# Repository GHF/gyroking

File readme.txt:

gyroking - firmware for the Gyro King 3lb battle bot
========
Xo Wang (http://www.geekshavefeelings.com)
Aaron Fan (http://aaronbot3000.blogspot.com)

About
-----
:D

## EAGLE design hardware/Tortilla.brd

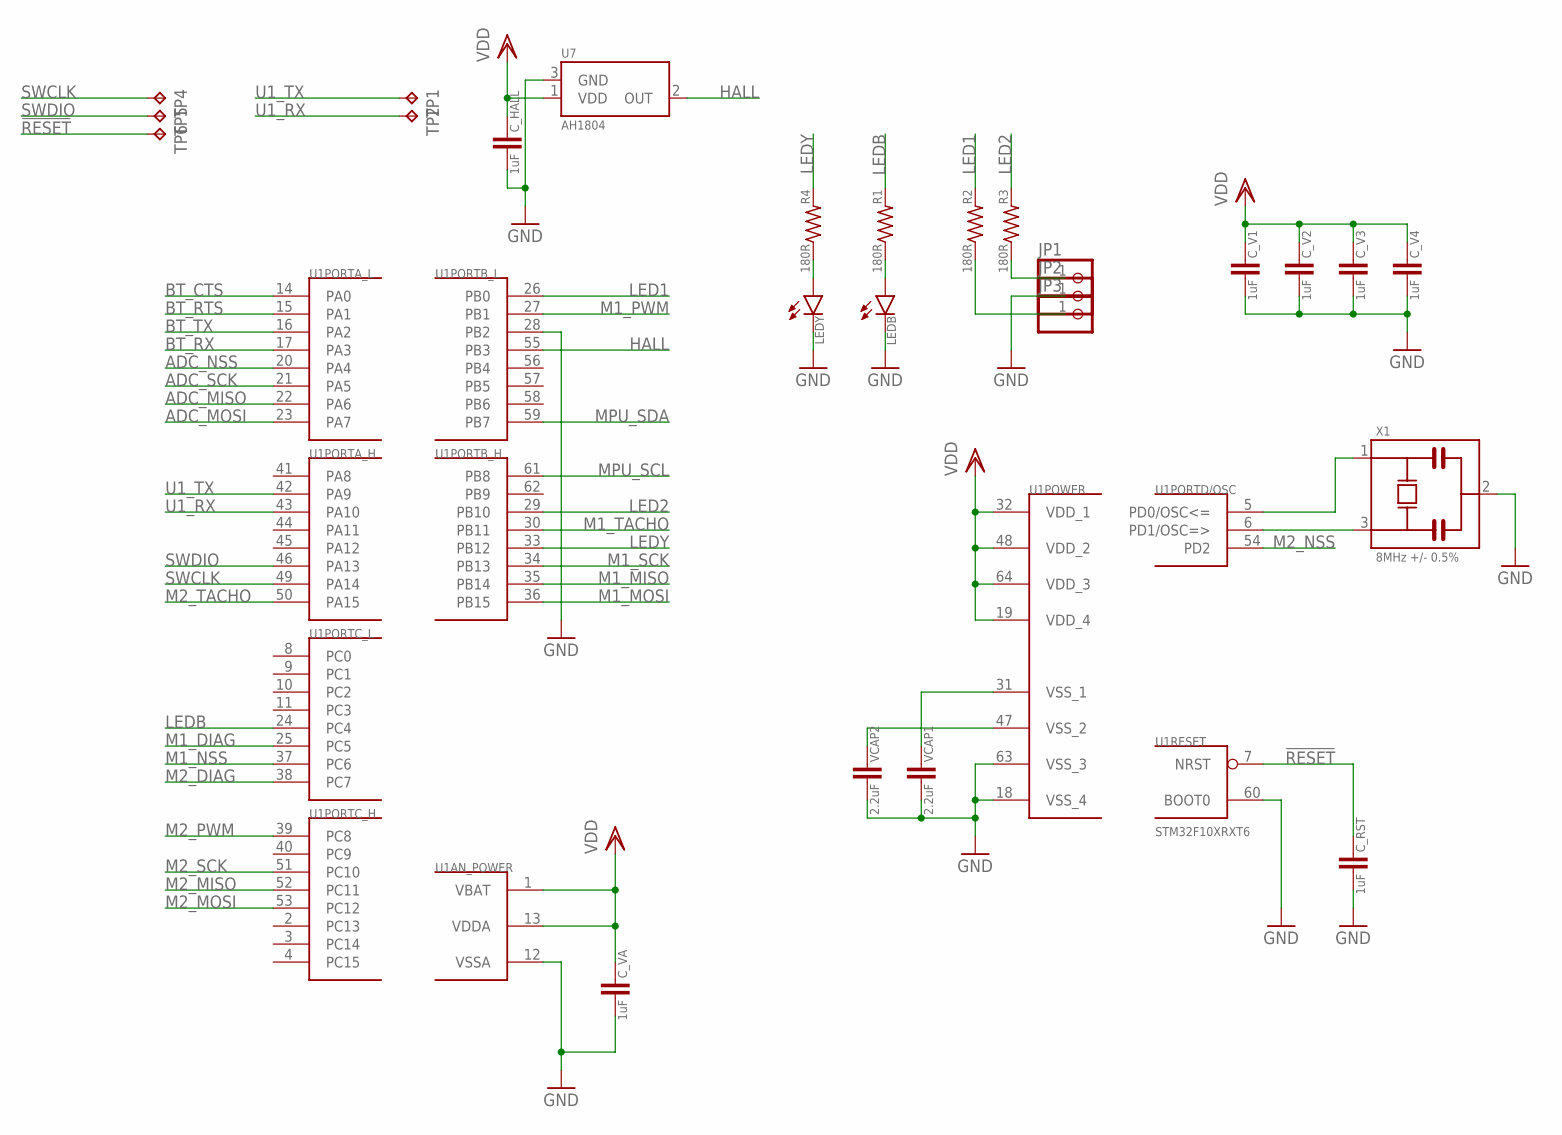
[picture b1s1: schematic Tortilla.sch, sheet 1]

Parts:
C_HALL: 1uF; 0603
C_RST: 1uF; 0603
C_V1, C_V2, C_V3, C_V4: 1uF; 0603
C_VA: 1uF; 0603
JP1, JP2, JP3: PINHD-1X1; 1X01
LEDB: LED0805; 0805_POL
LEDY: LED0805; 0805_POL
R1, R2, R3, R4: 180R; 0603
TP1, TP2, TP4, TP5, TP6: TPB1,27; B1,27
U1: STM32F10XRXT6; TQFP64
U7: AH1804; SOT23-3
VCAP1, VCAP2: 2.2uF; 0603
X1: 8MHz +/- 0.5%; MURATA_CSTCE

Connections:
!RESET: C_RST.1, TP6.TP, U1.7 (NRST)
ADC_MISO: U1.22 (PA6); also elsewhere on the board
ADC_MOSI: U1.23 (PA7); also elsewhere on the board
ADC_NSS: U1.20 (PA4); also elsewhere on the board
ADC_SCK: U1.21 (PA5); also elsewhere on the board
BT_CTS: U1.14 (PA0); also elsewhere on the board
BT_RTS: U1.15 (PA1); also elsewhere on the board
BT_RX: U1.17 (PA3); also elsewhere on the board
BT_TX: U1.16 (PA2); also elsewhere on the board
GND: C_HALL.2, C_RST.2, C_V1.2, C_V2.2, C_V3.2, C_V4.2, C_VA.2, JP2.1, LEDB.- (C), LEDY.- (C), U1.12 (VSSA), U1.18 (VSS_4), U1.28 (PB2), U1.60 (BOOT0), U1.63 (VSS_3), U7.3 (GND), VCAP1.2, VCAP2.2, X1.2; also elsewhere on the board
HALL: U1.55 (PB3), U7.2 (OUT)
LED1: R2.2, U1.26 (PB0)
LED2: R3.2, U1.29 (PB10)
LEDB: R1.2, U1.24 (PC4)
LEDY: R4.2, U1.33 (PB12)
M1_DIAG: U1.25 (PC5); also elsewhere on the board
M1_MISO: U1.35 (PB14); also elsewhere on the board
M1_MOSI: U1.36 (PB15); also elsewhere on the board
M1_NSS: U1.37 (PC6); also elsewhere on the board
M1_PWM: U1.27 (PB1); also elsewhere on the board
M1_SCK: U1.34 (PB13); also elsewhere on the board
M1_TACHO: U1.30 (PB11); also elsewhere on the board
M2_DIAG: U1.38 (PC7); also elsewhere on the board
M2_MISO: U1.52 (PC11); also elsewhere on the board
M2_MOSI: U1.53 (PC12); also elsewhere on the board
M2_NSS: U1.54 (PD2); also elsewhere on the board
M2_PWM: U1.39 (PC8); also elsewhere on the board
M2_SCK: U1.51 (PC10); also elsewhere on the board
M2_TACHO: U1.50 (PA15); also elsewhere on the board
MPU_SCL: U1.61 (PB8); also elsewhere on the board
MPU_SDA: U1.59 (PB7); also elsewhere on the board
unnamed: U1.6 (PD1/OSC=>), X1.3
unnamed: U1.5 (PD0/OSC<=), X1.1
unnamed: U1.47 (VSS_2), VCAP2.1
unnamed: U1.31 (VSS_1), VCAP1.1
unnamed: LEDB.+ (A), R1.1
unnamed: JP1.1, R3.1
unnamed: JP3.1, R2.1
unnamed: LEDY.+ (A), R4.1
SWCLK: TP4.TP, U1.49 (PA14)
SWDIO: TP5.TP, U1.46 (PA13)
U1_RX: TP2.TP, U1.43 (PA10)
U1_TX: TP1.TP, U1.42 (PA9)
VDD: C_HALL.1, C_V1.1, C_V2.1, C_V3.1, C_V4.1, C_VA.1, U1.1 (VBAT), U1.13 (VDDA), U1.19 (VDD_4), U1.32 (VDD_1), U1.48 (VDD_2), U1.64 (VDD_3), U7.1 (VDD); also elsewhere on the board

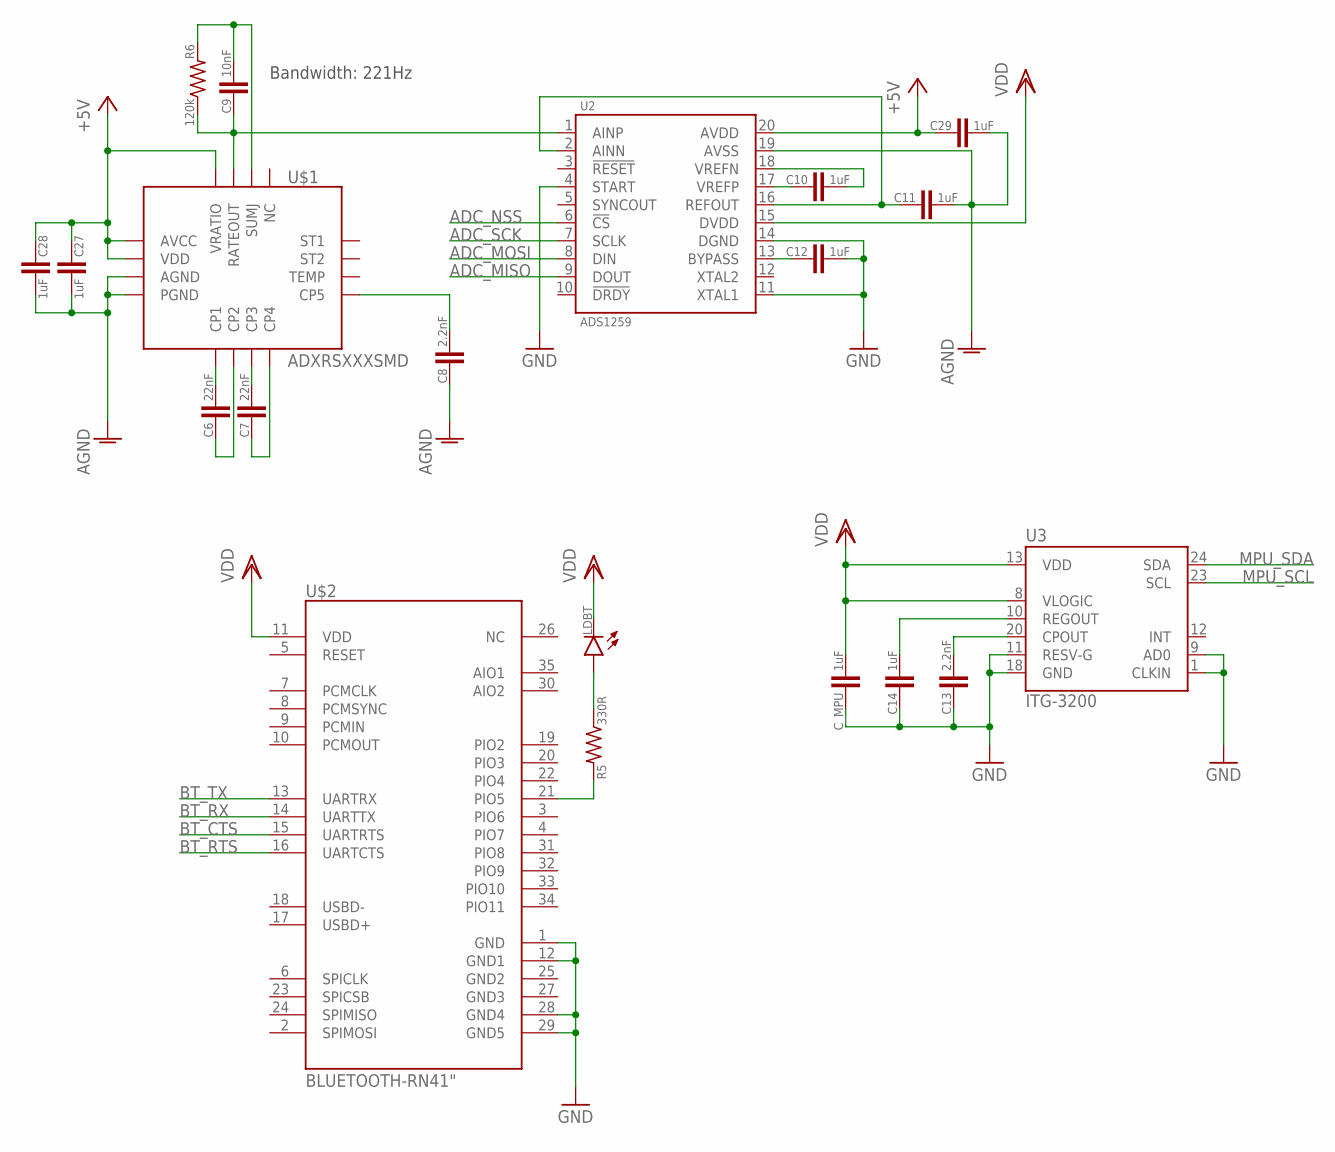
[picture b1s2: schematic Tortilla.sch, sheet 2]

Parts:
C6, C7: 22nF; 0603
C8, C13: 2.2nF; 0603
C9: 10nF; 0603
C10, C11, C12, C14, C27, C28, C29: 1uF; 0603
C_MPU: 1uF; 0603
LDBT: LED0805; 0805_POL
R5: 330R; 0603
R6: 120k; 0603
U2: ADS1259; TSSOP-20
U3: ITG-3200; QFN-24
U$1: ADXRSXXXSMD; BC-32
U$2: BLUETOOTH-RN41"; RN41

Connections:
+5V: C27.1, C28.1, C29.1, U2.20 (AVDD), U$1.AVCC, U$1.VDD, U$1.VRATIO; also elsewhere on the board
ADC_MISO: U2.9 (DOUT); also elsewhere on the board
ADC_MOSI: U2.8 (DIN); also elsewhere on the board
ADC_NSS: U2.6 (!CS); also elsewhere on the board
ADC_SCK: U2.7 (SCLK); also elsewhere on the board
AGND: C8.1, C11.2, C27.2, C28.2, C29.2, U2.19 (AVSS), U$1.AGND, U$1.PGND; also elsewhere on the board
BT_CTS: U$2.15 (UARTRTS); also elsewhere on the board
BT_RTS: U$2.16 (UARTCTS); also elsewhere on the board
BT_RX: U$2.14 (UARTTX); also elsewhere on the board
BT_TX: U$2.13 (UARTRX); also elsewhere on the board
GND: C12.2, C13.1, C14.1, C_MPU.1, U2.4 (START), U2.11 (XTAL1), U2.14 (DGND), U3.1 (CLKIN), U3.9 (AD0), U3.11 (RESV-G), U3.18 (GND), U$2.1 (GND), U$2.12 (GND1), U$2.28 (GND4), U$2.29 (GND5); also elsewhere on the board
MPU_SCL: U3.23 (SCL); also elsewhere on the board
MPU_SDA: U3.24 (SDA); also elsewhere on the board
unnamed: C6.2, U$1.CP1
unnamed: C6.1, U$1.CP2
unnamed: C7.2, U$1.CP3
unnamed: C7.1, U$1.CP4
unnamed: C8.2, U$1.CP5
unnamed: C9.1, R6.1, U2.1 (AINP), U$1.RATEOUT
unnamed: C9.2, R6.2, U$1.SUMJ
unnamed: C11.1, U2.2 (AINN), U2.16 (REFOUT)
unnamed: C10.2, U2.18 (VREFN)
unnamed: C10.1, U2.17 (VREFP)
unnamed: C12.1, U2.13 (BYPASS)
unnamed: C13.2, U3.20 (CPOUT)
unnamed: C14.2, U3.10 (REGOUT)
unnamed: R5.2, U$2.21 (PIO5)
unnamed: LDBT.+ (A), R5.1
VDD: C_MPU.2, LDBT.- (C), U2.15 (DVDD), U3.8 (VLOGIC), U3.13 (VDD), U$2.11 (VDD); also elsewhere on the board

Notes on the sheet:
Bandwidth: 221Hz

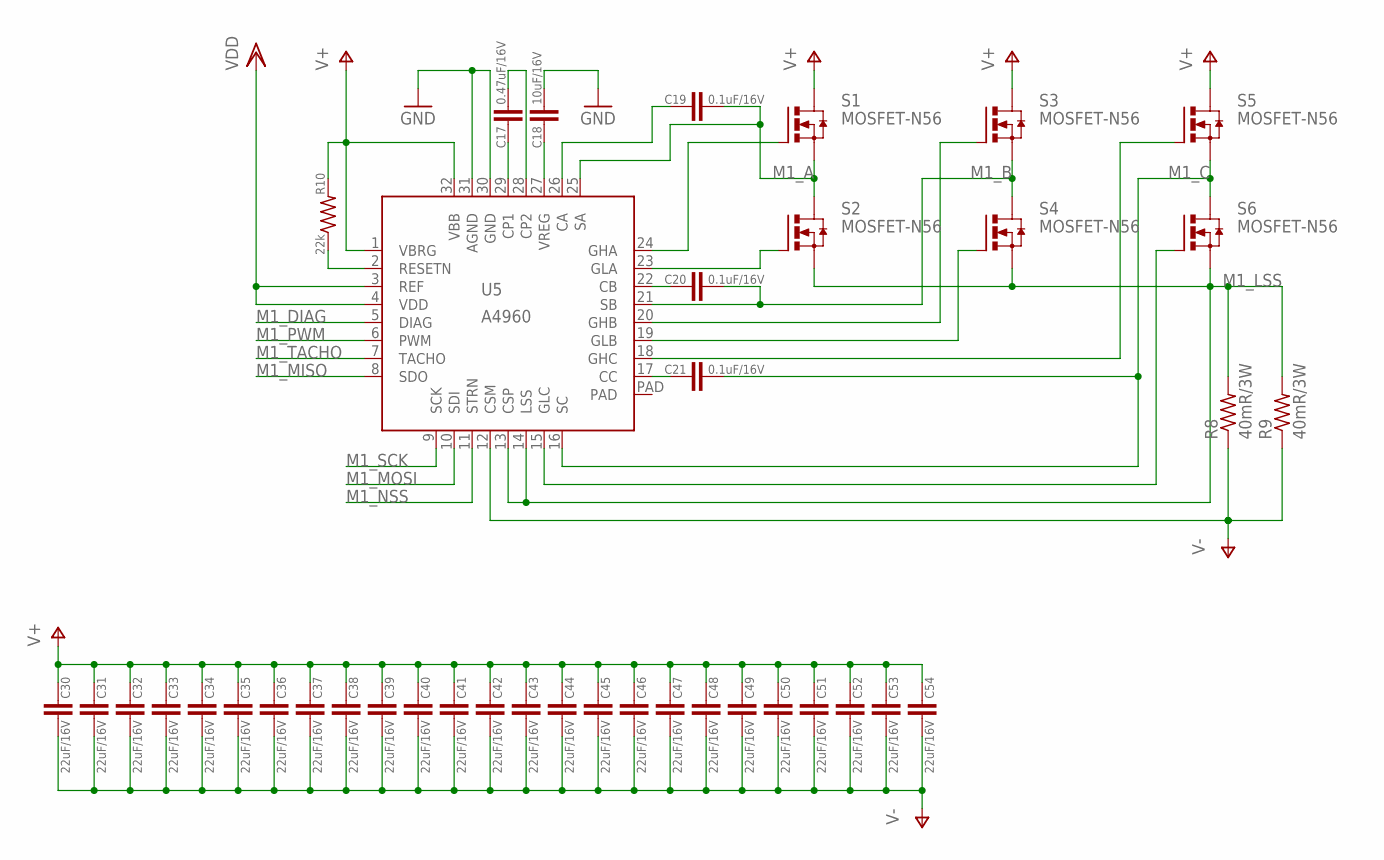
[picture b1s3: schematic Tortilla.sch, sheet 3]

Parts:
C17: 0.47uF/16V; 0603
C18: 10uF/16V; 0805
C19, C20, C21: 0.1uF/16V; 0603
C30, C31, C32, C33, C34, C35, C36, C37, C38, C39, C40, C41, C42, C43, C44, C45, C46, C47, C48, C49, C50, C51, C52, C53, C54: 22uF/16V; 1206
R8, R9: 40mR/3W; R2512
R10: 22k; 0603
S1, S2, S3, S4, S5, S6: MOSFET-N56; SON-5X6
U5: A4960; LQFP32-THERMPAD

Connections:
GND: C18.2, U5.30 (GND), U5.31 (AGND); also elsewhere on the board
M1_A: C19.2, S1.S1 (S), S1.S2 (S), S1.S3 (S), S2.D, U5.25 (SA)
M1_B: C20.2, S3.S1 (S), S3.S2 (S), S3.S3 (S), S4.D, U5.21 (SB)
M1_C: C21.2, S5.S1 (S), S5.S2 (S), S5.S3 (S), S6.D, U5.16 (SC)
M1_DIAG: U5.5 (DIAG); also elsewhere on the board
M1_LSS: R8.2, R9.2, S2.S1 (S), S2.S2 (S), S2.S3 (S), S4.S1 (S), S4.S2 (S), S4.S3 (S), S6.S1 (S), S6.S2 (S), S6.S3 (S), U5.13 (CSP), U5.14 (LSS)
M1_MISO: U5.8 (SDO); also elsewhere on the board
M1_MOSI: U5.10 (SDI); also elsewhere on the board
M1_NSS: U5.11 (STRN); also elsewhere on the board
M1_PWM: U5.6 (PWM); also elsewhere on the board
M1_SCK: U5.9 (SCK); also elsewhere on the board
M1_TACHO: U5.7 (TACHO); also elsewhere on the board
unnamed: C17.1, U5.29 (CP1)
unnamed: C17.2, U5.28 (CP2)
unnamed: C18.1, U5.27 (VREG)
unnamed: S1.G, U5.24 (GHA)
unnamed: S2.G, U5.23 (GLA)
unnamed: C19.1, U5.26 (CA)
unnamed: S3.G, U5.20 (GHB)
unnamed: S4.G, U5.19 (GLB)
unnamed: C20.1, U5.22 (CB)
unnamed: S5.G, U5.18 (GHC)
unnamed: S6.G, U5.15 (GLC)
unnamed: C21.1, U5.17 (CC)
unnamed: R10.1, U5.2 (RESETN)
V+: C30.1, C31.1, C32.1, C33.1, C34.1, C35.1, C36.1, C37.1, C38.1, C39.1, C40.1, C41.1, C42.1, C43.1, C44.1, C45.1, C46.1, C47.1, C48.1, C49.1, C50.1, C51.1, C52.1, C53.1, C54.1, R10.2, S1.D, S3.D, S5.D, U5.1 (VBRG), U5.32 (VBB); also elsewhere on the board
V-: C30.2, C31.2, C32.2, C33.2, C34.2, C35.2, C36.2, C37.2, C38.2, C39.2, C40.2, C41.2, C42.2, C43.2, C44.2, C45.2, C46.2, C47.2, C48.2, C49.2, C50.2, C51.2, C52.2, C53.2, C54.2, R8.1, R9.1, U5.12 (CSM); also elsewhere on the board
VDD: U5.3 (REF), U5.4 (VDD); also elsewhere on the board

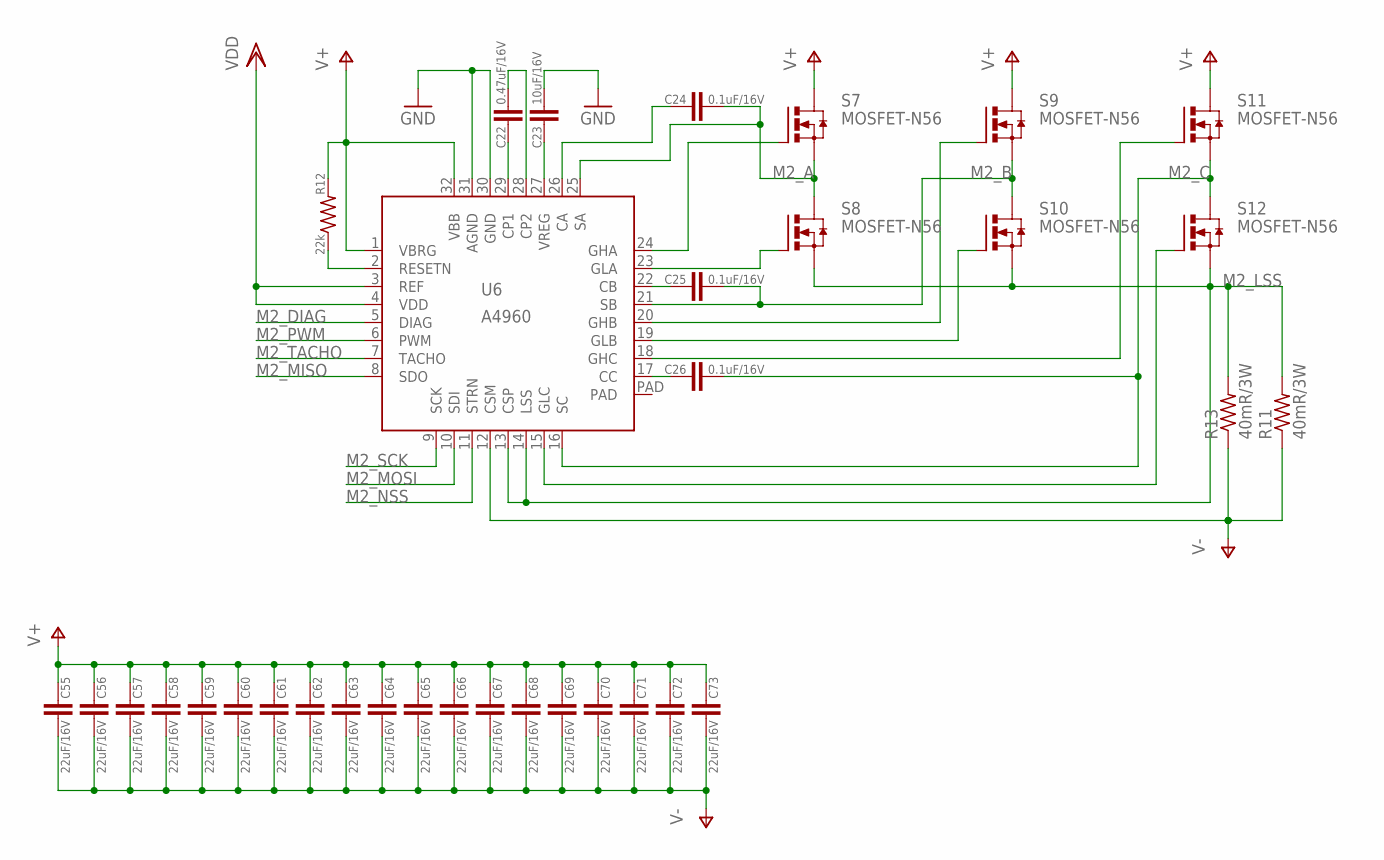
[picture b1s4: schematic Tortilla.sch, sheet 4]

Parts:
C22: 0.47uF/16V; 0603
C23: 10uF/16V; 0805
C24, C25, C26: 0.1uF/16V; 0603
C55, C56, C57, C58, C59, C60, C61, C62, C63, C64, C65, C66, C67, C68, C69, C70, C71, C72, C73: 22uF/16V; 1206
R11, R13: 40mR/3W; R2512
R12: 22k; 0603
S7, S8, S9, S10, S11, S12: MOSFET-N56; SON-5X6
U6: A4960; LQFP32-THERMPAD

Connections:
GND: C23.2, U6.30 (GND), U6.31 (AGND); also elsewhere on the board
M2_A: C24.2, S7.S1 (S), S7.S2 (S), S7.S3 (S), S8.D, U6.25 (SA)
M2_B: C25.2, S9.S1 (S), S9.S2 (S), S9.S3 (S), S10.D, U6.21 (SB)
M2_C: C26.2, S11.S1 (S), S11.S2 (S), S11.S3 (S), S12.D, U6.16 (SC)
M2_DIAG: U6.5 (DIAG); also elsewhere on the board
M2_LSS: R11.2, R13.2, S8.S1 (S), S8.S2 (S), S8.S3 (S), S10.S1 (S), S10.S2 (S), S10.S3 (S), S12.S1 (S), S12.S2 (S), S12.S3 (S), U6.13 (CSP), U6.14 (LSS)
M2_MISO: U6.8 (SDO); also elsewhere on the board
M2_MOSI: U6.10 (SDI); also elsewhere on the board
M2_NSS: U6.11 (STRN); also elsewhere on the board
M2_PWM: U6.6 (PWM); also elsewhere on the board
M2_SCK: U6.9 (SCK); also elsewhere on the board
M2_TACHO: U6.7 (TACHO); also elsewhere on the board
unnamed: C22.2, U6.28 (CP2)
unnamed: C22.1, U6.29 (CP1)
unnamed: C23.1, U6.27 (VREG)
unnamed: S7.G, U6.24 (GHA)
unnamed: S8.G, U6.23 (GLA)
unnamed: C24.1, U6.26 (CA)
unnamed: S9.G, U6.20 (GHB)
unnamed: S10.G, U6.19 (GLB)
unnamed: C25.1, U6.22 (CB)
unnamed: S11.G, U6.18 (GHC)
unnamed: S12.G, U6.15 (GLC)
unnamed: C26.1, U6.17 (CC)
unnamed: R12.1, U6.2 (RESETN)
V+: C55.1, C56.1, C57.1, C58.1, C59.1, C60.1, C61.1, C62.1, C63.1, C64.1, C65.1, C66.1, C67.1, C68.1, C69.1, C70.1, C71.1, C72.1, C73.1, R12.2, S7.D, S9.D, S11.D, U6.1 (VBRG), U6.32 (VBB); also elsewhere on the board
V-: C55.2, C56.2, C57.2, C58.2, C59.2, C60.2, C61.2, C62.2, C63.2, C64.2, C65.2, C66.2, C67.2, C68.2, C69.2, C70.2, C71.2, C72.2, C73.2, R11.1, R13.1, U6.12 (CSM); also elsewhere on the board
VDD: U6.3 (REF), U6.4 (VDD); also elsewhere on the board

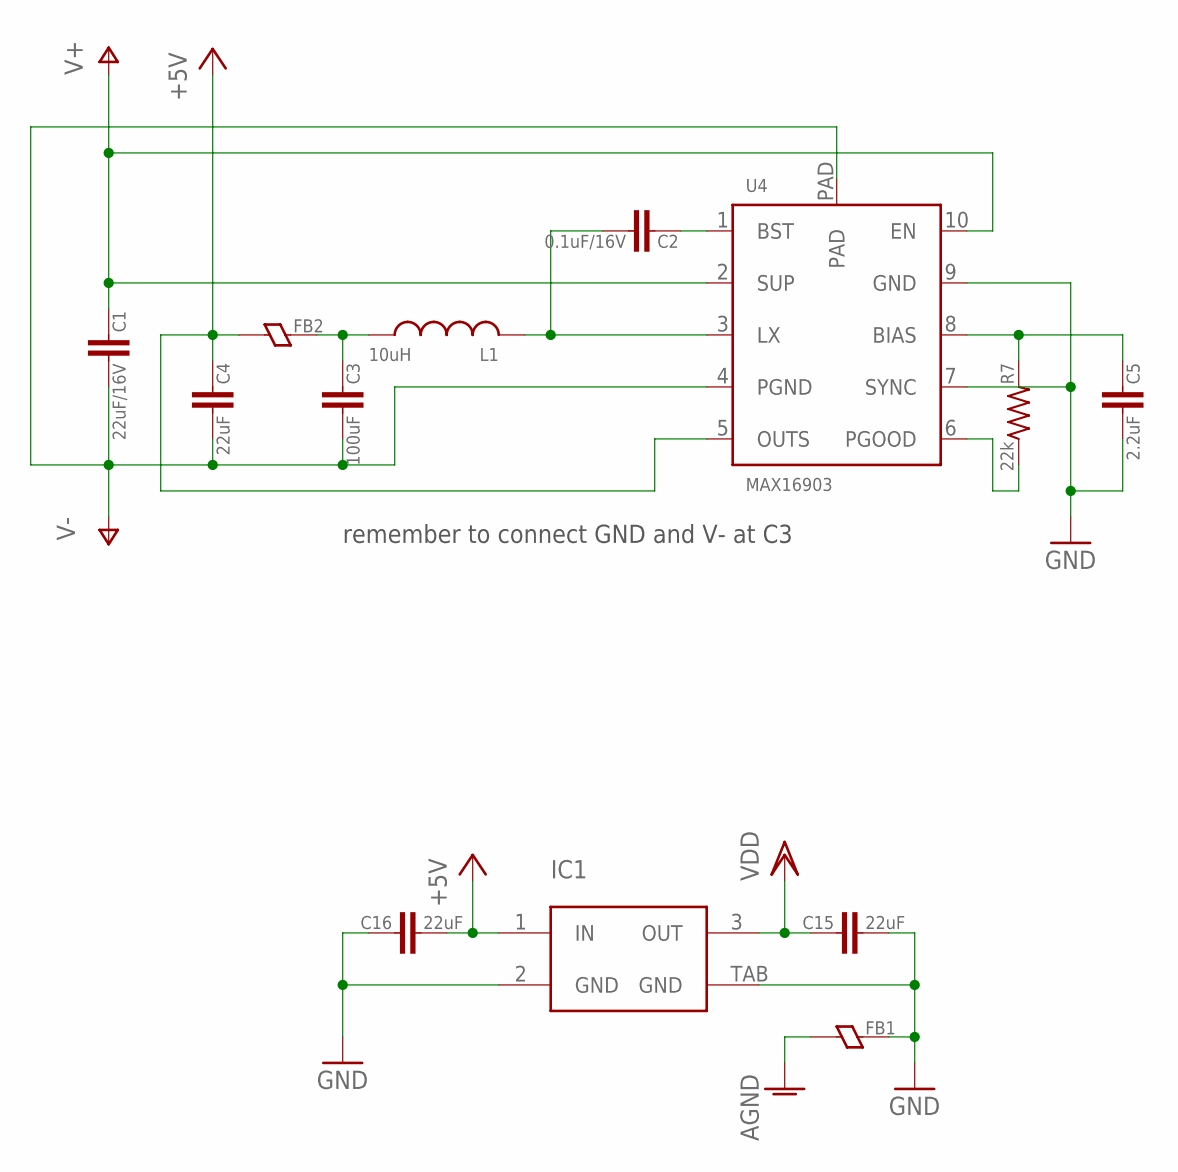
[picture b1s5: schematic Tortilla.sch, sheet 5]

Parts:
C1: 22uF/16V; 0805
C2: 0.1uF/16V; 0603
C3: 100uF; 1206
C4, C15, C16: 22uF; 0805
C5: 2.2uF; 0603
FB1, FB2: FERRITE0603; 0603
IC1: MCP1826S; SOT223-3L
L1: 10uH; TAIYO-YUDEN_NR30
R7: 22k; 0603
U4: MAX16903; TDFN-10

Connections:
+5V: C4.1, C16.2, FB2.1, IC1.1 (IN), U4.5 (OUTS); also elsewhere on the board
AGND: FB1.1; also elsewhere on the board
GND: C5.2, C15.2, C16.1, FB1.2, IC1.2 (GND), IC1.TAB (GND), U4.7 (SYNC), U4.9 (GND); also elsewhere on the board
unnamed: C2.1, U4.1 (BST)
unnamed: C2.2, L1.2, U4.3 (LX)
unnamed: C3.1, FB2.2, L1.1
unnamed: C5.1, R7.2, U4.8 (BIAS)
unnamed: R7.1, U4.6 (PGOOD)
V+: C1.1, U4.2 (SUP), U4.10 (EN); also elsewhere on the board
V-: C1.2, C3.2, C4.2, U4.4 (PGND), U4.PAD; also elsewhere on the board
VDD: C15.1, IC1.3 (OUT); also elsewhere on the board

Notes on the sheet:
remember to connect GND and V- at C3

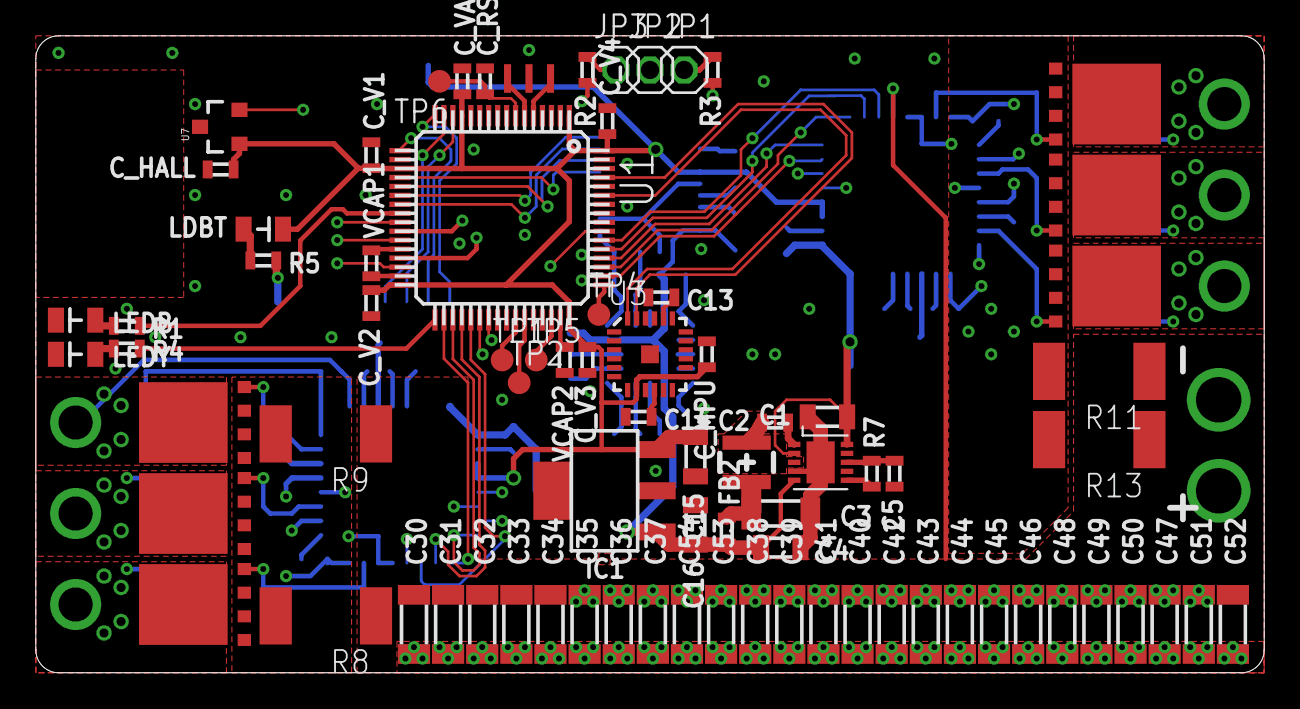
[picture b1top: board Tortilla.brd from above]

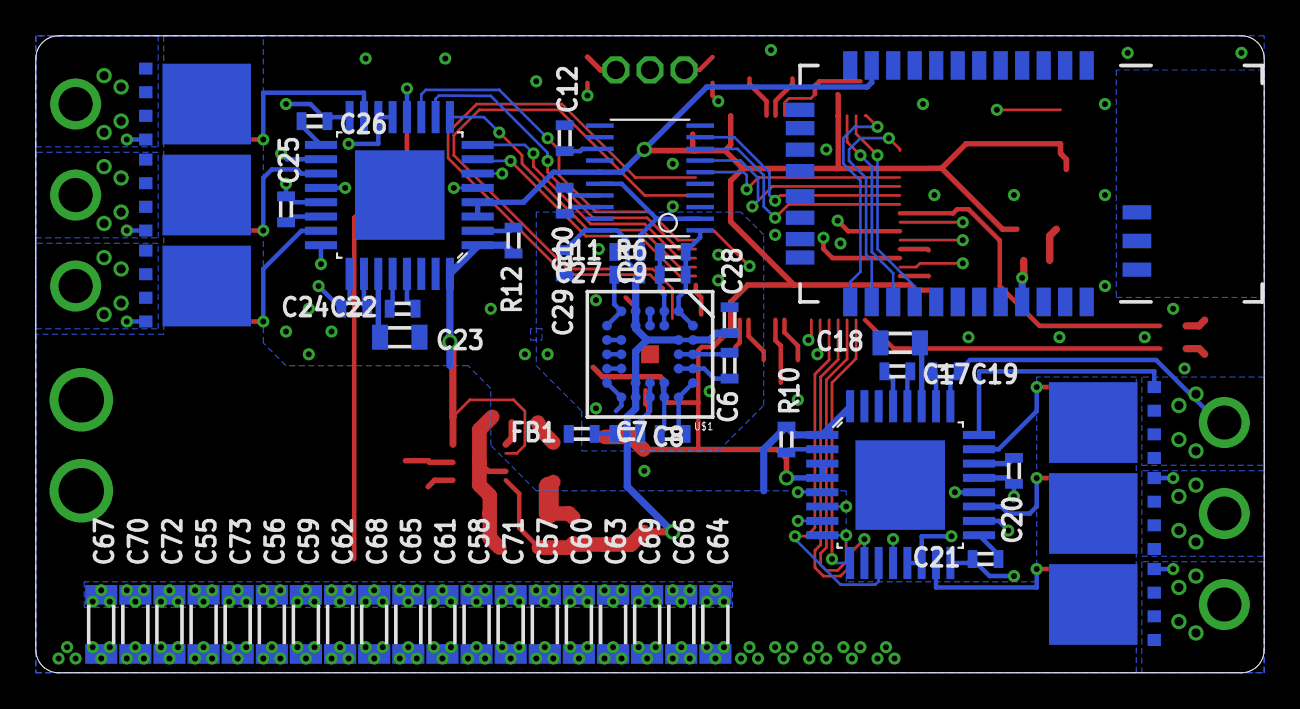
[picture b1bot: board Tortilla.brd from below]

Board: 4 copper layers, 68.6 x 35.6 mm, 133 parts (54 on the bottom side), 102 nets.

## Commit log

2012-10-05 Add board files and blink LEDs project
2012-10-05 Changed directory strcuture, added README & .gitignore
2012-10-06 Add A4960/K control code
2012-10-06 Add ADC reading code, turn on FPU
2012-10-10 Add custom edge-triggered ICU driver and gyro_pope command processor; change compile options for snprintf, M_PI, and std math libs
2012-10-10 Moved Tortilla v2.0 board files to top-level directory
2012-10-14 All sorts of tweaks to get the bot running and displaying a pointer
2012-10-14 Fix reverse bug, add joystick display, add joystick control; it melts now! Also split Tortilla class into two compilation units.
2012-10-25 Various changes to finalize functionality prior to GMX
2012-12-03 Add PCB design in hardware directory
2013-03-10 Add the 3D model files

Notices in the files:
parts and their libraries:
SparkFun-Sensors: Licensing: CC v3.0 Share-Alike You are welcome to use this library for commercial purposes.
